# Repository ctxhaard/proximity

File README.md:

# HCSR04 Ultrasound proximity sensor Linux driver
Developed for **Linux kernel 4.14**

- linux driver
- device tree
- test program

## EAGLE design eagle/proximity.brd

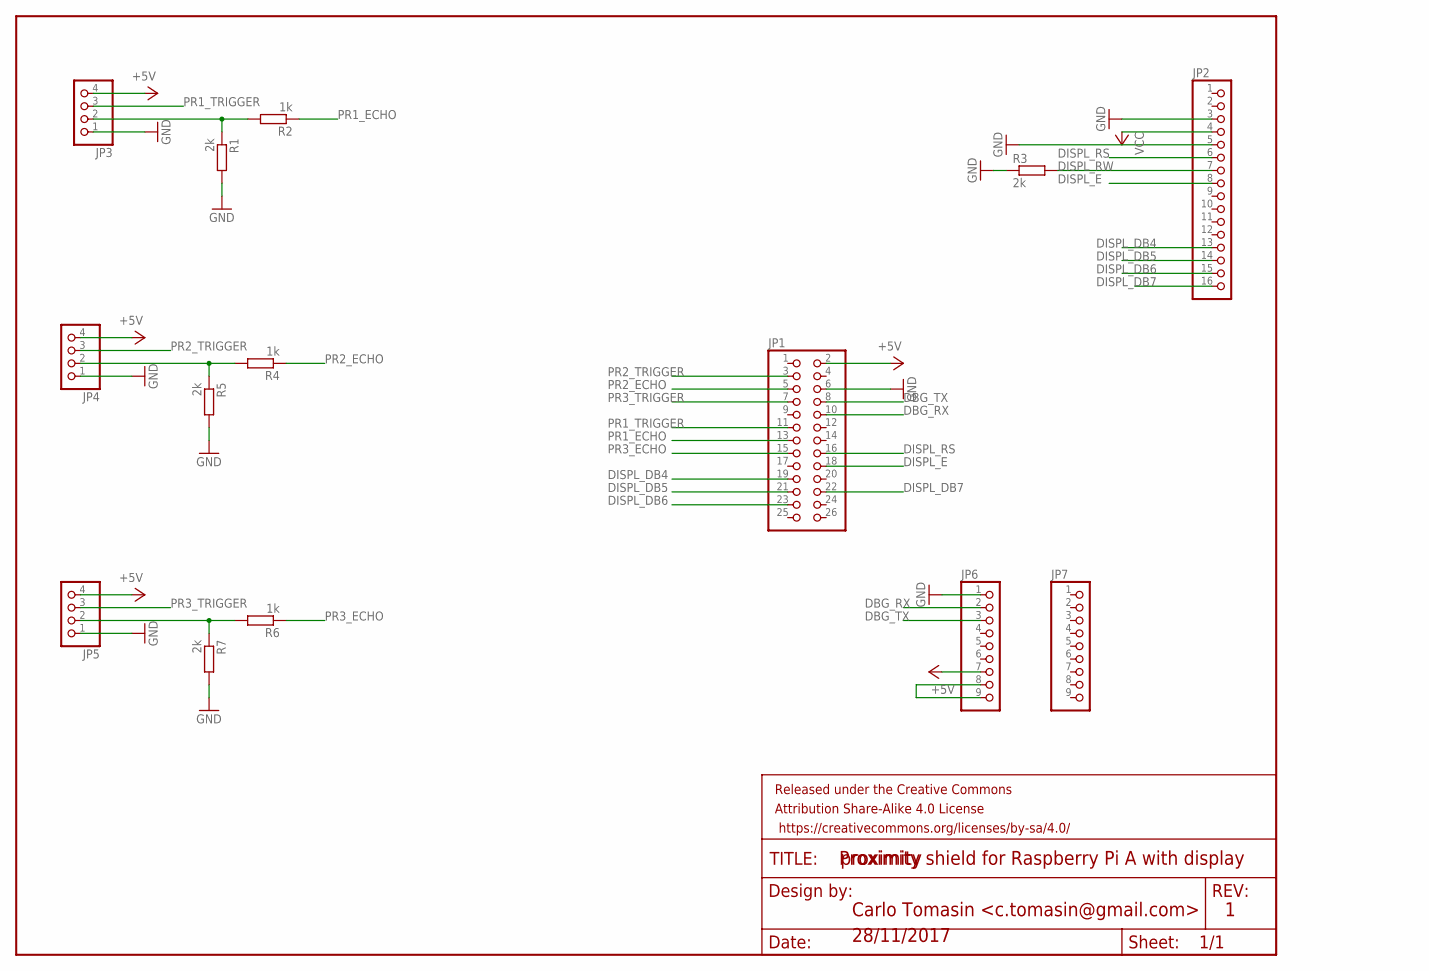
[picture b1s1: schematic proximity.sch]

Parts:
FRAME1: FRAME-LETTER; CREATIVE_COMMONS
JP1: PINHD-2X13; 2X13
JP2: PINHD-1X16; 1X16
JP3, JP4, JP5: PINHD-1X4; 1X04
JP6, JP7: PINHD-1X9; 1X09
R1, R3, R5, R7: 2k; 0204/7
R2, R4, R6: 1k; 0204/7

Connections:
+5V: JP1.2, JP3.4, JP4.4, JP5.4, JP6.7
DBG_RX: JP1.10, JP6.2
DBG_TX: JP1.8, JP6.3
DISPL_DB4: JP1.19, JP2.13
DISPL_DB5: JP1.21, JP2.14
DISPL_DB6: JP1.23, JP2.15
DISPL_DB7: JP1.22, JP2.16
DISPL_E: JP1.18, JP2.8
DISPL_RS: JP1.16, JP2.6
DISPL_RW: JP2.7, R3.2
GND: JP1.6, JP2.3, JP2.5, JP3.1, JP4.1, JP5.1, JP6.1, R1.2, R3.1, R5.2, R7.2
unnamed: JP3.2, R1.1, R2.2
unnamed: JP4.2, R4.2, R5.1
unnamed: JP5.2, R6.2, R7.1
unnamed: JP6.8, JP6.9
PR1_ECHO: JP1.13, R2.1
PR1_TRIGGER: JP1.11, JP3.3
PR2_ECHO: JP1.5, R4.1
PR2_TRIGGER: JP1.3, JP4.3
PR3_ECHO: JP1.15, R6.1
PR3_TRIGGER: JP1.7, JP5.3
VCC: JP2.4

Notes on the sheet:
Proximity shield for Raspberry Pi A with display
Carlo Tomasin <c.tomasin@gmail.com>
28/11/2017

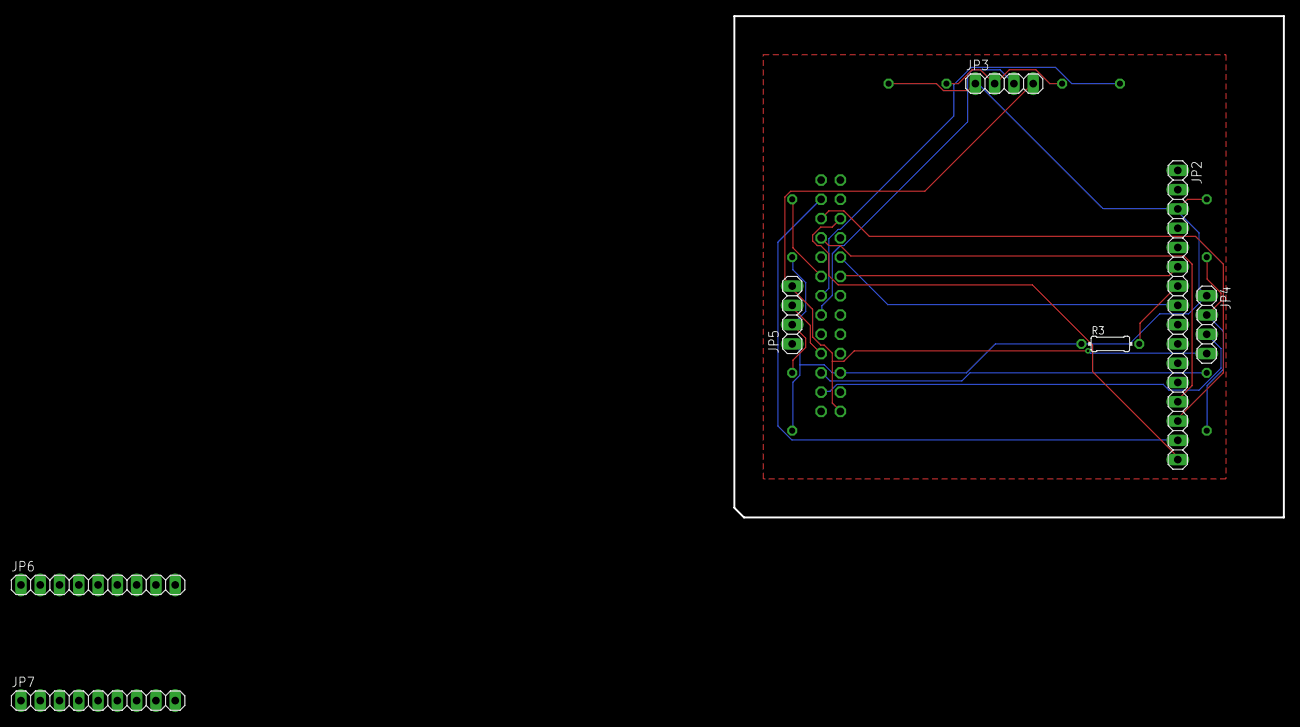
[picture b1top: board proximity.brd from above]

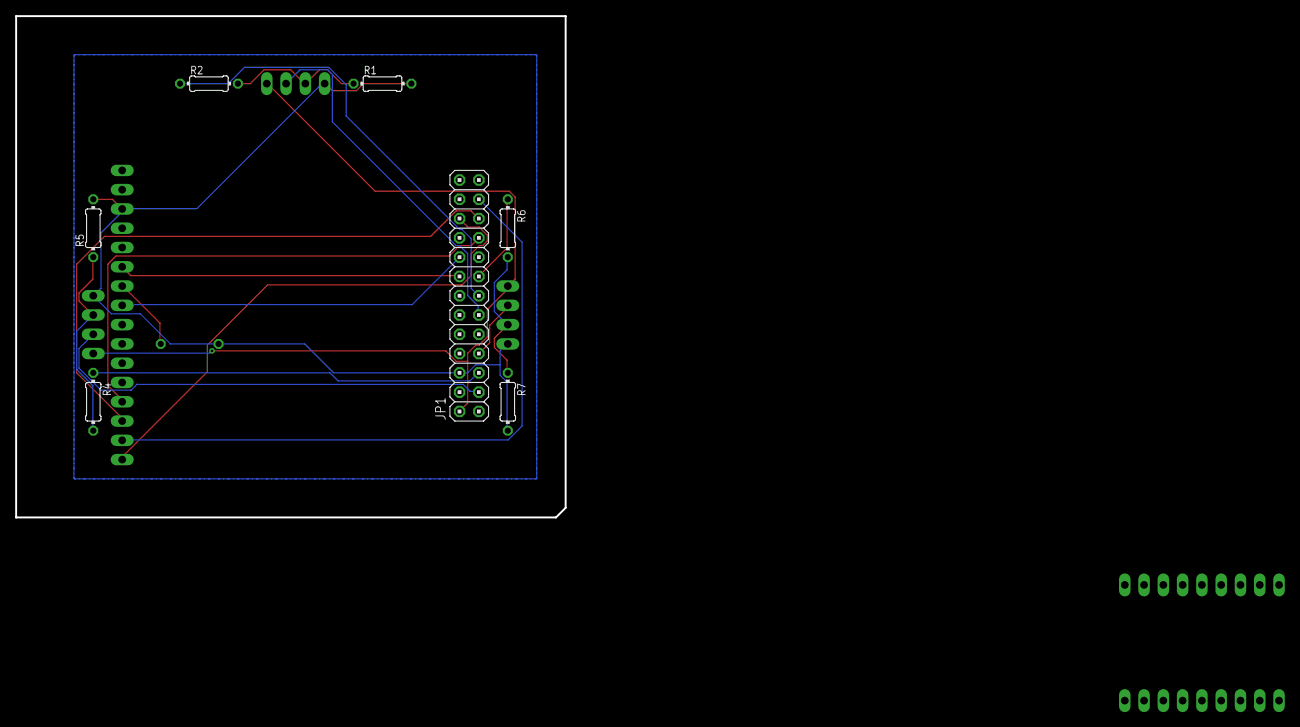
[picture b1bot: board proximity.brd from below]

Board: 2 copper layers, 72.4 x 66.0 mm, 15 parts (7 on the bottom side), 21 nets.

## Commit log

2016-09-08 First commit; it is working well apart a segmentation fault when removing the module
2016-09-15 hcsr04.c
2016-09-15 bugfix
2016-09-20 I moved the device tree from the overlay to the board's dts, because I was not able to make overlay working
2016-10-12 added device tree for raspberry pi 2
2017-10-28 added eagle CAD schematic for a Rpi shield
2017-10-29 added PCB file
2017-10-30 added GND and +5V planes
2017-11-02 added USB to serial to schematic
2017-12-01 little change
2017-12-04 added average on measures to get a more stable value
2017-12-08 refactoring; ** NEED BUGFIX: OOOPS IN SHUTDOWN **
2017-12-09 refactoring ** STILL BUGGY **
2017-12-10 bugfixed
2017-12-10 final bugfix
2017-12-21 echo IRQ is shared because it is used by different gpio pins
2017-12-21 better in SMP
2017-12-22 added test program
2017-12-22 added README
2018-01-15 N. of averaged samples as module parameter (max 10)

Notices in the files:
parts and their libraries:
SparkFun-Aesthetics: Licensing: Creative Commons ShareAlike 4.0 International - https://creativecommons.org/licenses/by-sa/4.0
SparkFun-Aesthetics: Released under the Creative Commons Attribution Share-Alike 4.0 License
SparkFun-Aesthetics: https://creativecommons.org/licenses/by-sa/4.0
